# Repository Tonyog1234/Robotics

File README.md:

This repository is to store my work in robotics club at Concordia University.

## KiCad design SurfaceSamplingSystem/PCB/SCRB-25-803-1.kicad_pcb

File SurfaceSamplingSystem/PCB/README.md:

Surface Sampling System(SSS) is one of the subsystems for science payload.  
SSS controls four servo motors to scoop the dirt.  
When the scoop is closed, there is a holding torque(~50mA).  
When the scoop is open, the servo shouldn't consume any power.  
Only one scoop will be open at a time, and each servo should have current feedback to know if the holding torque is too much or not.  
This custom PCB has been reviewed by electrical lead of robotics club.

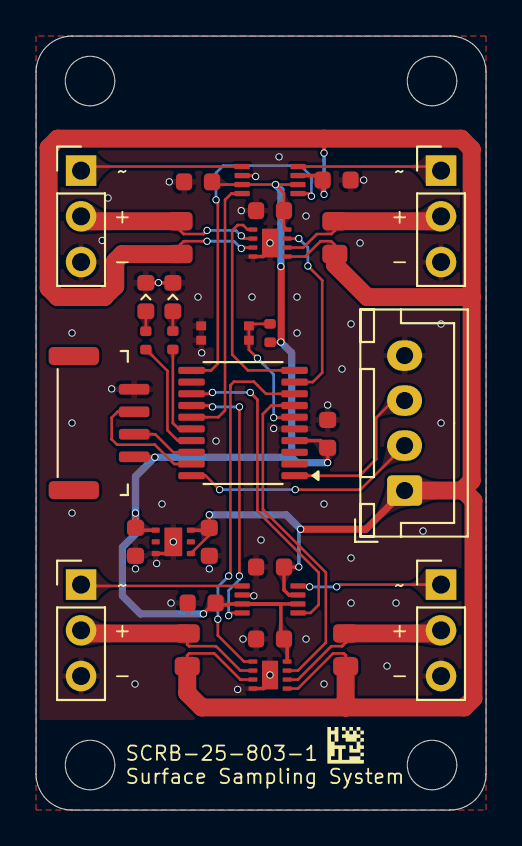
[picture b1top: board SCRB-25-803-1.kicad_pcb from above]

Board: 2 copper layers, 25.0 x 43.0 mm, 35 parts (0 on the bottom side), 28 nets.

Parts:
C1, C2: 4.7u; C0603
C3, C4, C5, C6, C7, C8, C9: 0.1uF; C0603
H1, H2, H3, H4: Hole_M2.5
J1: EDIF-4; JST-GH-BM04B-GHS-TBT
J2, J3, J4, J5: Conn_01x03_Socket; PinHeader_1x03_P2.54mm_Vertical
JST_XH4: Conn_01x04_Pin; JST_XH_B4B-XH-A_1x04_P2.50mm_Vertical
LD1, LD2: LED0603
R1, R2, R7: 10k; R0402
R3, R4, R5, R6: 140m, 250mW; R0805
SW1: SW_Tiny; SW_C913791
U1, U4: TXB0102DCUR; DCU0008A
U2, U3: INA2180A1IDSGR; DSG0008A
U6: TLV75533PDRVR; DRV0006A
U7: STM32G030F6; TSSOP-20_4.4x6.5mm_P0.65mm

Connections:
+3.3V: C2.1, C3.1, C4.1, C5.1, C6.1, C7.1, J1.1 (3.3V), R7.1, U1.3 (VCCA), U1.6 (OE), U2.8 (VS), U3.8 (VS), U4.3 (VCCA), U4.6 (OE), U6.1 (OUT), U7.4 (VDD)
+5V: C1.1, C8.1, C9.1, JST_XH4.1, R3.1, R4.1, R5.1, R6.1, U1.7 (VCCB), U2.3 (IN+1), U2.5 (IN+2), U3.3 (IN+1), U3.5 (IN+2), U4.7 (VCCB), U6.4 (EN), U6.6 (IN)
/ADC0: U2.7 (OUT2), U7.7 (PA0)
/ADC1: U2.1 (OUT1), U7.8 (PA1)
/ADC2: U3.7 (OUT2), U7.9 (PA2)
/ADC3: U3.1 (OUT1), U7.10 (PA3)
/PWM_IN1: U1.5 (A1), U7.13 (PA6)
/PWM_IN2: U1.4 (A2), U7.14 (PA7)
/PWM_IN3: U4.5 (A1), U7.11 (PA4)
/PWM_IN4: U4.4 (A2), U7.15 (PB0/PB1/PB2/PA8)
/PWM_OUT1: J2.1, U1.8 (B1)
/PWM_OUT2: J5.1, U1.1 (B2)
/PWM_OUT3: J3.1, U4.8 (B1)
/PWM_OUT4: J4.1, U4.1 (B2)
/R3_out: J5.2, R3.2, U2.2 (IN-1)
/R4_out: J2.2, R4.2, U2.6 (IN-2)
/R5_out: J3.2, R5.2, U3.6 (IN-2)
/R6_out: J4.2, R6.2, U3.2 (IN-1)
GND: C1.2, C2.2, C3.2, C4.2, C5.2, C6.2, C7.2, C8.2, C9.2, J1.4 (GND), J2.3, J3.3, J4.3, J5.3, JST_XH4.4, LD1.1 (K), LD2.1 (K), SW1.1, U1.2 (GND), U2.4 (GND), U2.9 (PAD), U3.4 (GND), U3.9 (PAD), U4.2 (GND), U6.3 (GND), U6.7 (PAD), U7.5 (VSS)
unnamed: J1.3 (SWC), U7.19 (PA14/PA15)
unnamed: J1.2 (SWD), U7.18 (PA13)
unnamed: JST_XH4.2, U7.20 (PB3/PB4/PB5/PB6)
unnamed: JST_XH4.3, U7.1 (PB7/PB8)
unnamed: LD1.2 (A), R1.2
unnamed: LD2.2 (A), R2.2
unnamed: R7.2, SW1.2, U7.6 (NRST)
unnamed: R1.1, U7.16 (PA11/PA9)
unnamed: R2.1, U7.17 (PA12/PA10)

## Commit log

2025-01-30 Create Surface Sampling System
2025-01-30 Rename Surface Sampling System to Surface_Sampling_System
2025-01-30 Create PCB
2025-01-30 Add files via upload
    Custom PCB
